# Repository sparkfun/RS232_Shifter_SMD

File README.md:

SparkFun RS232 Shifter SMD
===========================

[*RS232 Shifter SMD(PRT-00449)*](https://www.sparkfun.com/products/449)

This board converts RS232 to TTL and runs from 300 bps to 115200 bps. 
 This will allow a microcontroller to communicate with a computer. 
Shifter SMD is powered from the target application and can run at any voltage! 

Repository Contents
-------------------

* **/Hardware** - All Eagle design files (.brd, .sch)
* **/Production** - Production panel files (.brd)

Documentation
-------------------
* [Serial Communication](https://learn.sparkfun.com/tutorials/serial-communication) - Basic tutorial on serial communication implemented on logic-level (TTL) and RS-232.
* [RS-232 vs. TTL Serial Communication](https://www.sparkfun.com/tutorials/215) - Short explanation about the logic levels and the hardware used to convert signals with the RS232 Shifter. 

Product Versions
----------------
* [PRT-08780](https://www.sparkfun.com/products/8780) - Shifter - no DB9 connector
* [PRT-00449](https://www.sparkfun.com/products/449) - Shifter with DB9 connector populated.

Version History
---------------

* [v1.4](https://github.com/sparkfun/RS232_Shifter_SMD/tree/V_1.4) - GitHub version 1.4. Retired for a more production friendly version.

License Information
-------------------

This product is _**open source**_! 

Please review the LICENSE.md file for license information. 

If you have any questions or concerns on licensing, please contact techsupport@sparkfun.com.

Distributed as-is; no warranty is given.

- Your friends at SparkFun.

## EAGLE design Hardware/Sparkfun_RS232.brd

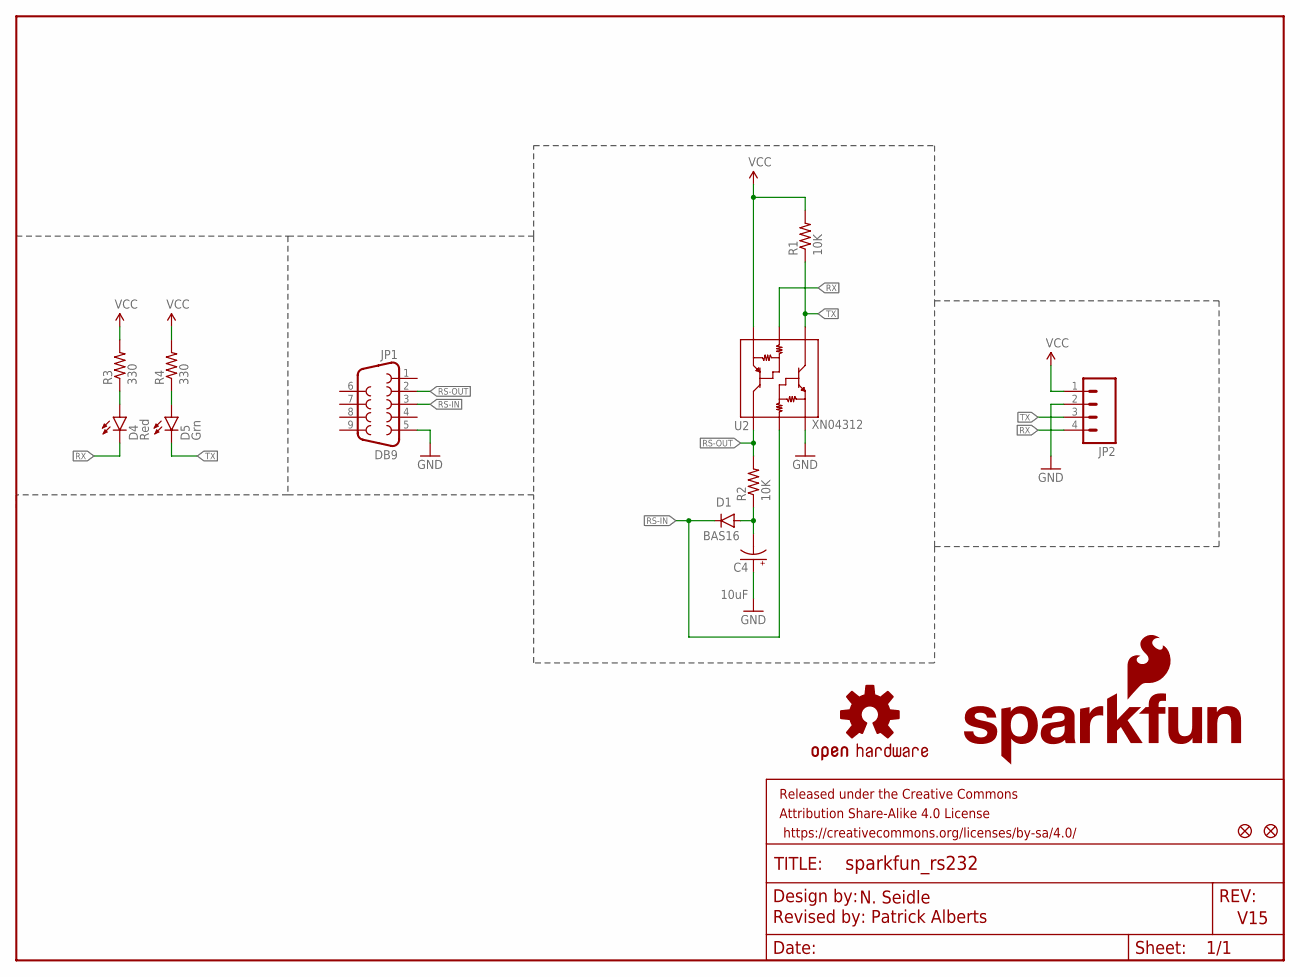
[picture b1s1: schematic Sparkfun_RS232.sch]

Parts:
C4: 10uF; EIA3216
D1: BAS16; SOD-323
D4: Red; LED-1206
D5: Grn; LED-1206
E$1, E$2: FIDUCIAL1X2; FIDUCIAL-1X2
FRAME1: FRAME-LETTER; CREATIVE_COMMONS
JP1: DB9
JP2: M04PTH; 1X04
LOGO1: SFE_LOGO_NAME_FLAME.1_INCH; SFE_LOGO_NAME_FLAME_.1
LOGO2: OSHW-LOGOM; OSHW-LOGO-M
R1, R2: 10K; 0603-RES
R3, R4: 330; 0603-RES
U2: XN04312; SOT23-6

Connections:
GND: C4.A (+), JP1.5, JP2.2, U2.6 (E1)
unnamed: D4.A, R3.1
unnamed: D5.A, R4.1
unnamed: C4.C (-), D1.A, R2.1
RS-IN: D1.C, JP1.3, U2.5 (B1)
RS-OUT: JP1.2, R2.2, U2.4 (C2)
RX: D4.C, JP2.4, U2.2 (B2)
TX: D5.C, JP2.3, R1.1, U2.1 (C1)
VCC: JP2.1, R1.2, R3.2, R4.2, U2.3 (E2)

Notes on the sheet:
V15
Revised by: Patrick Alberts
N. Seidle

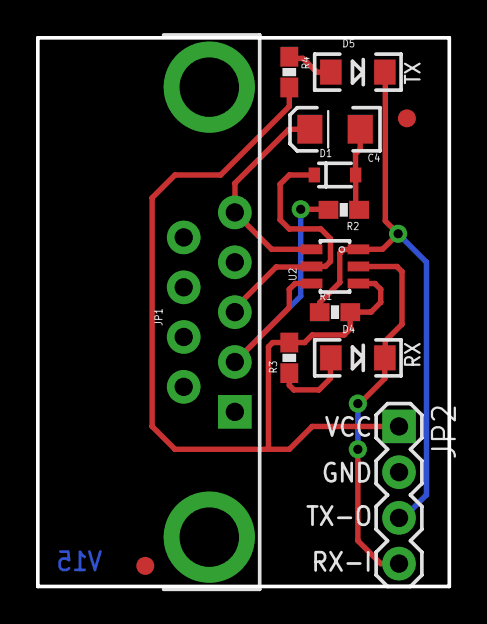
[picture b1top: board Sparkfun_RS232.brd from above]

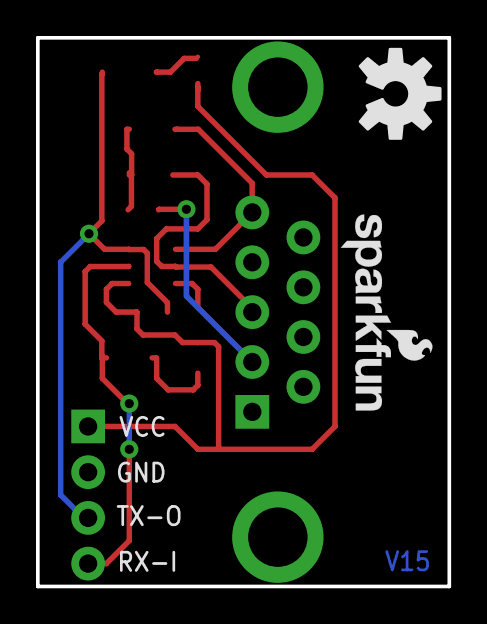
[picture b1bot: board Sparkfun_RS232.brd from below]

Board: 2 copper layers, 22.9 x 30.5 mm, 16 parts (2 on the bottom side), 9 nets.

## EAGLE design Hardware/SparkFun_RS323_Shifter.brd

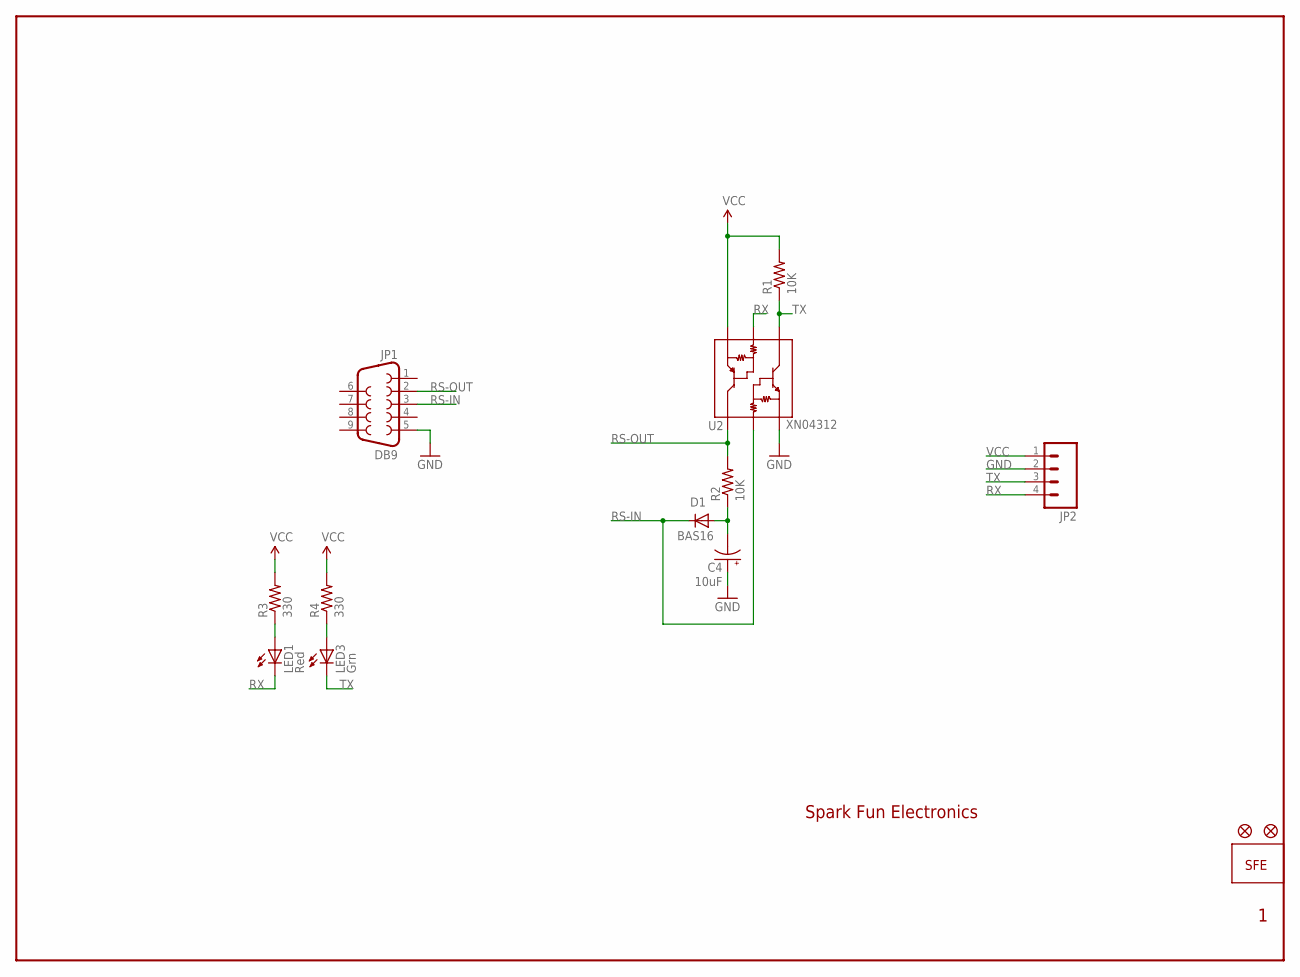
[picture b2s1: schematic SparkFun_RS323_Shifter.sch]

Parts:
C4: 10uF; EIA3216
D1: BAS16; SOD-323
E$1, E$2: FIDUCIAL1X2; FIDUCIAL-1X2
JP1: DB9
JP2: M04PTH; 1X04
LED1: Red; LED-1206
LED3: Grn; LED-1206
R1, R2: 10K; 0603-RES
R3, R4: 330; 0603-RES
U2: XN04312; SOT23-6
U$1: LOGO-SFENEW; SFE-NEW-WEBLOGO

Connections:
GND: C4.A (+), JP1.5, JP2.2, U2.6 (E1)
unnamed: LED1.A, R3.1
unnamed: LED3.A, R4.1
unnamed: C4.C (-), D1.2 (A), R2.1
RS-IN: D1.1 (C), JP1.3, U2.5 (B1)
RS-OUT: JP1.2, R2.2, U2.4 (C2)
RX: JP2.4, LED1.C, U2.2 (B2)
TX: JP2.3, LED3.C, R1.1, U2.1 (C1)
VCC: JP2.1, R1.2, R3.2, R4.2, U2.3 (E2)

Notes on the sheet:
Spark Fun Electronics

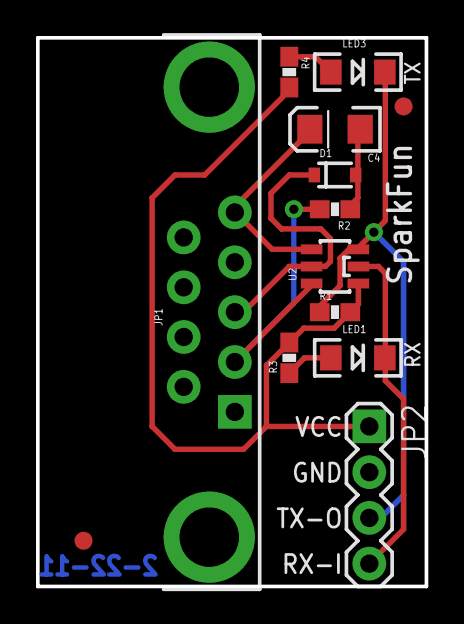
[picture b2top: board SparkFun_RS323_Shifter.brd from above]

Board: 2 copper layers, 21.6 x 30.5 mm, 14 parts (1 on the bottom side), 9 nets.

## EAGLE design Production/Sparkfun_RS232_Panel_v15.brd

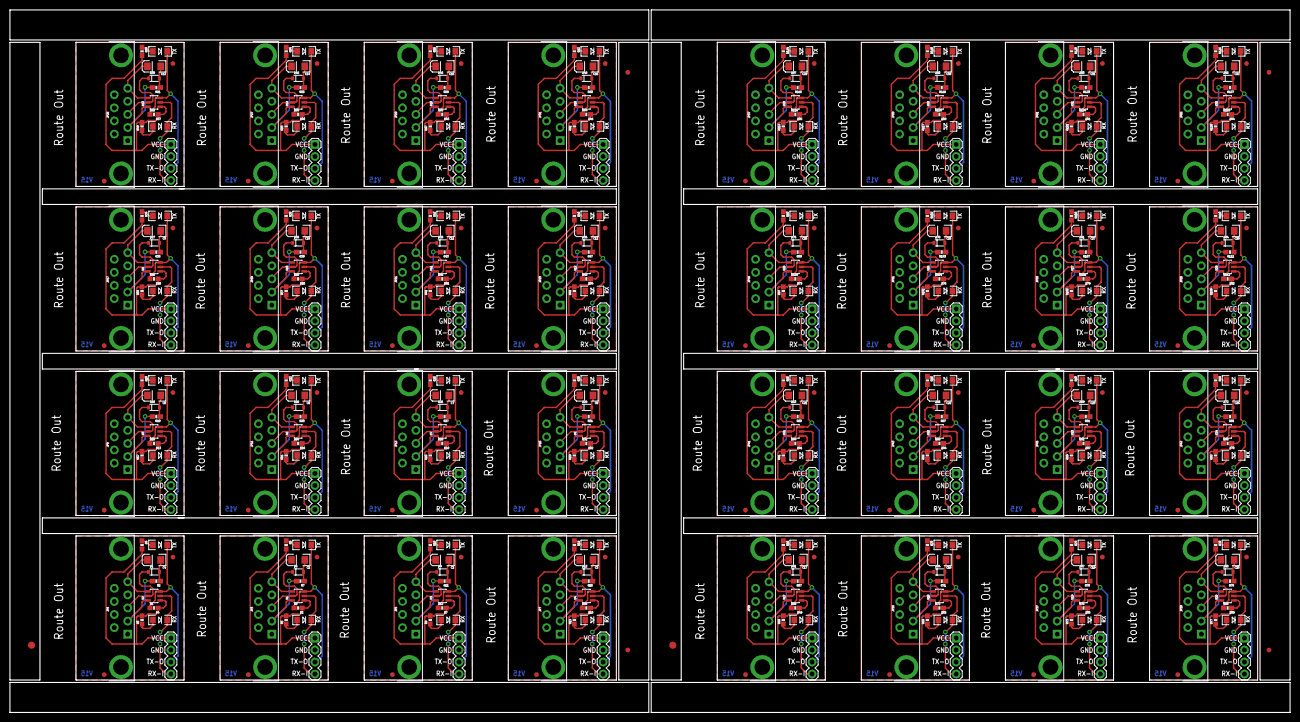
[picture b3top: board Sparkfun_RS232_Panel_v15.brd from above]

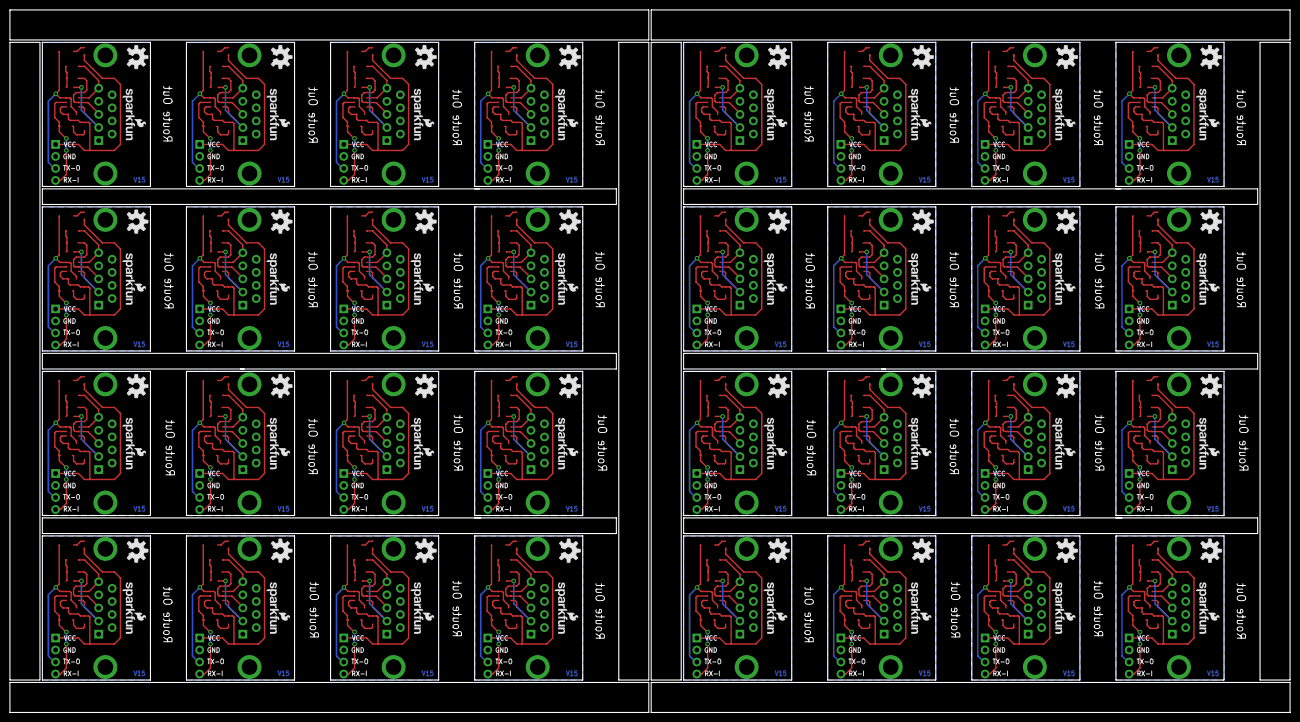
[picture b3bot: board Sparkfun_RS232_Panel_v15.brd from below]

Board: 2 copper layers, 270.8 x 148.6 mm, 486 parts (64 on the bottom side), 288 nets.

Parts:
C1, C2, C3, C4, C5, C6, C7, C8, C9, C10, C11, C12, C13, C14, C15, C16, C17, C18, C19, C20, C21, C22, C23, C24, C25, C26, C27, C28, C29, C30, C31, C32: 10uF; EIA3216
D1, D6, D9, D12, D15, D18, D21, D24, D27, D30, D33, D36, D39, D42, D45, D48, D51, D54, D57, D60, D63, D66, D69, D72, D75, D78, D81, D84, D87, D90, D93, D96: BAS16; SOD-323
D2, D4, D7, D10, D13, D16, D19, D22, D25, D28, D31, D34, D37, D40, D43, D46, D49, D52, D55, D58, D61, D64, D67, D70, D73, D76, D79, D82, D85, D88, D91, D94: Red; LED-1206
D3, D5, D8, D11, D14, D17, D20, D23, D26, D29, D32, D35, D38, D41, D44, D47, D50, D53, D56, D59, D62, D65, D68, D71, D74, D77, D80, D83, D86, D89, D92, D95: Grn; LED-1206
E$1, E$2, E$3, E$4, E$5, E$6, E$7, E$8, E$9, E$10, E$11, E$12, E$13, E$14, E$15, E$16, E$17, E$18, E$19, E$20, E$21, E$22, E$23, E$24, E$25, E$26, E$27, E$28, E$29, E$30, E$31, E$32, E$34, E$35, E$36, E$37, E$38, E$39, E$40, E$41, E$44, E$45, E$46, E$47, E$48, E$49, E$50, E$51, E$52, E$53, E$54, E$55, E$56, E$57, E$58, E$59, E$60, E$61, E$62, E$63, E$64, E$65, E$66, E$67: FIDUCIAL1X2; FIDUCIAL-1X2
E$33, E$70: FIDUCIAL-1.5X3
E$42, E$43, E$68, E$69: FIDUCIAL-1X2
JP1, JP3, JP5, JP7, JP9, JP11, JP13, JP15, JP17, JP19, JP21, JP23, JP25, JP27, JP29, JP31, JP33, JP35, JP37, JP39, JP41, JP43, JP45, JP47, JP49, JP51, JP53, JP55, JP57, JP59, JP61, JP63: DB9
JP2, JP4, JP6, JP8, JP10, JP12, JP14, JP16, JP18, JP20, JP22, JP24, JP26, JP28, JP30, JP32, JP34, JP36, JP38, JP40, JP42, JP44, JP46, JP48, JP50, JP52, JP54, JP56, JP58, JP60, JP62, JP64: 1X04
LOGO1, LOGO4, LOGO6, LOGO8, LOGO10, LOGO12, LOGO14, LOGO16, LOGO18, LOGO20, LOGO22, LOGO24, LOGO26, LOGO28, LOGO30, LOGO32, LOGO34, LOGO36, LOGO38, LOGO40, LOGO42, LOGO44, LOGO46, LOGO48, LOGO50, LOGO52, LOGO54, LOGO56, LOGO58, LOGO60, LOGO62, LOGO64: SFE_LOGO_NAME_FLAME.1_INCH; SFE_LOGO_NAME_FLAME_.1
LOGO2, LOGO3, LOGO5, LOGO7, LOGO9, LOGO11, LOGO13, LOGO15, LOGO17, LOGO19, LOGO21, LOGO23, LOGO25, LOGO27, LOGO29, LOGO31, LOGO33, LOGO35, LOGO37, LOGO39, LOGO41, LOGO43, LOGO45, LOGO47, LOGO49, LOGO51, LOGO53, LOGO55, LOGO57, LOGO59, LOGO61, LOGO63: OSHW-LOGOM; OSHW-LOGO-M
R1, R2, R7, R8, R11, R12, R15, R16, R19, R20, R23, R24, R27, R28, R31, R32, R35, R36, R39, R40, R43, R44, R47, R48, R51, R52, R55, R56, R59, R60, R63, R64, R67, R68, R71, R72, R75, R76, R79, R80, R83, R84, R87, R88, R91, R92, R95, R96, R99, R100, R103, R104, R107, R108, R111, R112, R115, R116, R119, R120, R123, R124, R127, R128: 10K; 0603-RES
R3, R4, R5, R6, R9, R10, R13, R14, R17, R18, R21, R22, R25, R26, R29, R30, R33, R34, R37, R38, R41, R42, R45, R46, R49, R50, R53, R54, R57, R58, R61, R62, R65, R66, R69, R70, R73, R74, R77, R78, R81, R82, R85, R86, R89, R90, R93, R94, R97, R98, R101, R102, R105, R106, R109, R110, R113, R114, R117, R118, R121, R122, R125, R126: 330; 0603-RES
U1, U2, U3, U4, U5, U6, U7, U8, U9, U10, U11, U12, U13, U14, U15, U16, U17, U18, U19, U20, U21, U22, U23, U24, U25, U26, U27, U28, U29, U30, U31, U32: XN04312; SOT23-6

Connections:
GND: C4.A, JP1.5, JP2.2, U2.6
GND1: C1.A, JP3.5, JP4.2, U1.6
GND2: C2.A, JP5.5, JP6.2, U3.6
GND3: C3.A, JP7.5, JP8.2, U4.6
GND4: C5.A, JP9.5, JP10.2, U5.6
GND5: C6.A, JP11.5, JP12.2, U6.6
GND6: C7.A, JP13.5, JP14.2, U7.6
GND7: C8.A, JP15.5, JP16.2, U8.6
GND8: C9.A, JP17.5, JP18.2, U9.6
GND9: C10.A, JP19.5, JP20.2, U10.6
GND10: C11.A, JP21.5, JP22.2, U11.6
GND11: C12.A, JP23.5, JP24.2, U12.6
GND12: C13.A, JP25.5, JP26.2, U13.6
GND13: C14.A, JP27.5, JP28.2, U14.6
GND14: C15.A, JP29.5, JP30.2, U15.6
GND15: C16.A, JP31.5, JP32.2, U16.6
GND16: C17.A, JP33.5, JP34.2, U17.6
GND17: C18.A, JP35.5, JP36.2, U18.6
GND18: C19.A, JP37.5, JP38.2, U19.6
GND19: C20.A, JP39.5, JP40.2, U20.6
GND20: C21.A, JP41.5, JP42.2, U21.6
GND21: C22.A, JP43.5, JP44.2, U22.6
GND22: C23.A, JP45.5, JP46.2, U23.6
GND23: C24.A, JP47.5, JP48.2, U24.6
GND24: C25.A, JP49.5, JP50.2, U25.6
GND25: C26.A, JP51.5, JP52.2, U26.6
GND26: C27.A, JP53.5, JP54.2, U27.6
GND27: C28.A, JP55.5, JP56.2, U28.6
GND28: C29.A, JP57.5, JP58.2, U29.6
GND29: C30.A, JP59.5, JP60.2, U30.6
GND30: C31.A, JP61.5, JP62.2, U31.6
GND31: C32.A, JP63.5, JP64.2, U32.6
unnamed: D4.A, R3.1
unnamed: D5.A, R4.1
unnamed: D2.A, R5.1
unnamed: C4.C, D1.A, R2.1
unnamed: D3.A, R6.1
unnamed: C1.C, D6.A, R7.1
unnamed: D7.A, R9.1
unnamed: D8.A, R10.1
unnamed: C2.C, D9.A, R11.1
unnamed: D10.A, R13.1
unnamed: D11.A, R14.1
unnamed: C3.C, D12.A, R15.1
unnamed: D13.A, R17.1
unnamed: D14.A, R18.1
unnamed: C5.C, D15.A, R19.1
unnamed: D16.A, R21.1
unnamed: D17.A, R22.1
unnamed: C6.C, D18.A, R23.1
unnamed: D19.A, R25.1
unnamed: D20.A, R26.1
unnamed: C7.C, D21.A, R27.1
unnamed: D22.A, R29.1
unnamed: D23.A, R30.1
unnamed: C8.C, D24.A, R31.1
unnamed: D25.A, R33.1
unnamed: D26.A, R34.1
unnamed: C9.C, D27.A, R35.1
unnamed: D28.A, R37.1
unnamed: D29.A, R38.1
unnamed: C10.C, D30.A, R39.1
unnamed: D31.A, R41.1
unnamed: D32.A, R42.1
unnamed: C11.C, D33.A, R43.1
unnamed: D34.A, R45.1
unnamed: D35.A, R46.1
unnamed: C12.C, D36.A, R47.1
unnamed: D37.A, R49.1
unnamed: D38.A, R50.1
unnamed: C13.C, D39.A, R51.1
unnamed: D40.A, R53.1
unnamed: D41.A, R54.1
unnamed: C14.C, D42.A, R55.1
unnamed: D43.A, R57.1
unnamed: D44.A, R58.1
unnamed: C15.C, D45.A, R59.1
unnamed: D46.A, R61.1
unnamed: D47.A, R62.1
unnamed: C16.C, D48.A, R63.1
unnamed: D49.A, R65.1
unnamed: D50.A, R66.1
unnamed: C17.C, D51.A, R67.1
unnamed: D52.A, R69.1
unnamed: D53.A, R70.1
unnamed: C18.C, D54.A, R71.1
unnamed: D55.A, R73.1
unnamed: D56.A, R74.1
unnamed: C19.C, D57.A, R75.1
unnamed: D58.A, R77.1
unnamed: D59.A, R78.1
unnamed: C20.C, D60.A, R79.1
unnamed: D61.A, R81.1
unnamed: D62.A, R82.1
unnamed: C21.C, D63.A, R83.1
unnamed: D64.A, R85.1
unnamed: D65.A, R86.1
unnamed: C22.C, D66.A, R87.1
unnamed: D67.A, R89.1
unnamed: D68.A, R90.1
unnamed: C23.C, D69.A, R91.1
unnamed: D70.A, R93.1
unnamed: D71.A, R94.1
unnamed: C24.C, D72.A, R95.1
unnamed: D73.A, R97.1
unnamed: D74.A, R98.1
unnamed: C25.C, D75.A, R99.1
unnamed: D76.A, R101.1
unnamed: D77.A, R102.1
unnamed: C26.C, D78.A, R103.1
unnamed: D79.A, R105.1
unnamed: D80.A, R106.1
unnamed: C27.C, D81.A, R107.1
unnamed: D82.A, R109.1
unnamed: D83.A, R110.1
unnamed: C28.C, D84.A, R111.1
unnamed: D85.A, R113.1
unnamed: D86.A, R114.1
unnamed: C29.C, D87.A, R115.1
unnamed: D88.A, R117.1
unnamed: D89.A, R118.1
unnamed: C30.C, D90.A, R119.1
unnamed: D91.A, R121.1
unnamed: D92.A, R122.1
unnamed: C31.C, D93.A, R123.1
unnamed: D94.A, R125.1
unnamed: D95.A, R126.1
unnamed: C32.C, D96.A, R127.1
RS-IN: D1.C, JP1.3, U2.5
RS-IN1: D6.C, JP3.3, U1.5
RS-IN2: D9.C, JP5.3, U3.5
RS-IN3: D12.C, JP7.3, U4.5
RS-IN4: D15.C, JP9.3, U5.5
RS-IN5: D18.C, JP11.3, U6.5
RS-IN6: D21.C, JP13.3, U7.5
RS-IN7: D24.C, JP15.3, U8.5
RS-IN8: D27.C, JP17.3, U9.5
RS-IN9: D30.C, JP19.3, U10.5
RS-IN10: D33.C, JP21.3, U11.5
RS-IN11: D36.C, JP23.3, U12.5
RS-IN12: D39.C, JP25.3, U13.5
RS-IN13: D42.C, JP27.3, U14.5
RS-IN14: D45.C, JP29.3, U15.5
RS-IN15: D48.C, JP31.3, U16.5
RS-IN16: D51.C, JP33.3, U17.5
RS-IN17: D54.C, JP35.3, U18.5
RS-IN18: D57.C, JP37.3, U19.5
RS-IN19: D60.C, JP39.3, U20.5
RS-IN20: D63.C, JP41.3, U21.5
RS-IN21: D66.C, JP43.3, U22.5
RS-IN22: D69.C, JP45.3, U23.5
RS-IN23: D72.C, JP47.3, U24.5
RS-IN24: D75.C, JP49.3, U25.5
RS-IN25: D78.C, JP51.3, U26.5
RS-IN26: D81.C, JP53.3, U27.5
RS-IN27: D84.C, JP55.3, U28.5
RS-IN28: D87.C, JP57.3, U29.5
RS-IN29: D90.C, JP59.3, U30.5
RS-IN30: D93.C, JP61.3, U31.5
RS-IN31: D96.C, JP63.3, U32.5
RS-OUT: JP1.2, R2.2, U2.4
RS-OUT1: JP3.2, R7.2, U1.4
RS-OUT2: JP5.2, R11.2, U3.4
RS-OUT3: JP7.2, R15.2, U4.4
RS-OUT4: JP9.2, R19.2, U5.4
RS-OUT5: JP11.2, R23.2, U6.4
RS-OUT6: JP13.2, R27.2, U7.4
RS-OUT7: JP15.2, R31.2, U8.4
RS-OUT8: JP17.2, R35.2, U9.4
RS-OUT9: JP19.2, R39.2, U10.4
RS-OUT10: JP21.2, R43.2, U11.4
RS-OUT11: JP23.2, R47.2, U12.4
RS-OUT12: JP25.2, R51.2, U13.4
RS-OUT13: JP27.2, R55.2, U14.4
RS-OUT14: JP29.2, R59.2, U15.4
RS-OUT15: JP31.2, R63.2, U16.4
RS-OUT16: JP33.2, R67.2, U17.4
RS-OUT17: JP35.2, R71.2, U18.4
RS-OUT18: JP37.2, R75.2, U19.4
RS-OUT19: JP39.2, R79.2, U20.4
RS-OUT20: JP41.2, R83.2, U21.4
RS-OUT21: JP43.2, R87.2, U22.4
RS-OUT22: JP45.2, R91.2, U23.4
RS-OUT23: JP47.2, R95.2, U24.4
RS-OUT24: JP49.2, R99.2, U25.4
RS-OUT25: JP51.2, R103.2, U26.4
RS-OUT26: JP53.2, R107.2, U27.4
RS-OUT27: JP55.2, R111.2, U28.4
RS-OUT28: JP57.2, R115.2, U29.4
RS-OUT29: JP59.2, R119.2, U30.4
RS-OUT30: JP61.2, R123.2, U31.4
RS-OUT31: JP63.2, R127.2, U32.4
RX: D4.C, JP2.4, U2.2
RX1: D2.C, JP4.4, U1.2
RX2: D7.C, JP6.4, U3.2
RX3: D10.C, JP8.4, U4.2
RX4: D13.C, JP10.4, U5.2
RX5: D16.C, JP12.4, U6.2
RX6: D19.C, JP14.4, U7.2
RX7: D22.C, JP16.4, U8.2
RX8: D25.C, JP18.4, U9.2
RX9: D28.C, JP20.4, U10.2
RX10: D31.C, JP22.4, U11.2
RX11: D34.C, JP24.4, U12.2
RX12: D37.C, JP26.4, U13.2
RX13: D40.C, JP28.4, U14.2
RX14: D43.C, JP30.4, U15.2
RX15: D46.C, JP32.4, U16.2
RX16: D49.C, JP34.4, U17.2
RX17: D52.C, JP36.4, U18.2
RX18: D55.C, JP38.4, U19.2
RX19: D58.C, JP40.4, U20.2
RX20: D61.C, JP42.4, U21.2
RX21: D64.C, JP44.4, U22.2
RX22: D67.C, JP46.4, U23.2
RX23: D70.C, JP48.4, U24.2
RX24: D73.C, JP50.4, U25.2
RX25: D76.C, JP52.4, U26.2
RX26: D79.C, JP54.4, U27.2
RX27: D82.C, JP56.4, U28.2
RX28: D85.C, JP58.4, U29.2
RX29: D88.C, JP60.4, U30.2
RX30: D91.C, JP62.4, U31.2
RX31: D94.C, JP64.4, U32.2
TX: D5.C, JP2.3, R1.1, U2.1
TX1: D3.C, JP4.3, R8.1, U1.1
TX2: D8.C, JP6.3, R12.1, U3.1
TX3: D11.C, JP8.3, R16.1, U4.1
TX4: D14.C, JP10.3, R20.1, U5.1
TX5: D17.C, JP12.3, R24.1, U6.1
TX6: D20.C, JP14.3, R28.1, U7.1
TX7: D23.C, JP16.3, R32.1, U8.1
TX8: D26.C, JP18.3, R36.1, U9.1
TX9: D29.C, JP20.3, R40.1, U10.1
TX10: D32.C, JP22.3, R44.1, U11.1
TX11: D35.C, JP24.3, R48.1, U12.1
TX12: D38.C, JP26.3, R52.1, U13.1
TX13: D41.C, JP28.3, R56.1, U14.1
TX14: D44.C, JP30.3, R60.1, U15.1
TX15: D47.C, JP32.3, R64.1, U16.1
TX16: D50.C, JP34.3, R68.1, U17.1
TX17: D53.C, JP36.3, R72.1, U18.1
TX18: D56.C, JP38.3, R76.1, U19.1
TX19: D59.C, JP40.3, R80.1, U20.1
TX20: D62.C, JP42.3, R84.1, U21.1
TX21: D65.C, JP44.3, R88.1, U22.1
TX22: D68.C, JP46.3, R92.1, U23.1
TX23: D71.C, JP48.3, R96.1, U24.1
TX24: D74.C, JP50.3, R100.1, U25.1
TX25: D77.C, JP52.3, R104.1, U26.1
TX26: D80.C, JP54.3, R108.1, U27.1
TX27: D83.C, JP56.3, R112.1, U28.1
TX28: D86.C, JP58.3, R116.1, U29.1
TX29: D89.C, JP60.3, R120.1, U30.1
TX30: D92.C, JP62.3, R124.1, U31.1
TX31: D95.C, JP64.3, R128.1, U32.1
VCC: JP2.1, R1.2, R3.2, R4.2, U2.3
VCC1: JP4.1, R5.2, R6.2, R8.2, U1.3
VCC2: JP6.1, R9.2, R10.2, R12.2, U3.3
VCC3: JP8.1, R13.2, R14.2, R16.2, U4.3
VCC4: JP10.1, R17.2, R18.2, R20.2, U5.3
VCC5: JP12.1, R21.2, R22.2, R24.2, U6.3
VCC6: JP14.1, R25.2, R26.2, R28.2, U7.3
VCC7: JP16.1, R29.2, R30.2, R32.2, U8.3
VCC8: JP18.1, R33.2, R34.2, R36.2, U9.3
VCC9: JP20.1, R37.2, R38.2, R40.2, U10.3
VCC10: JP22.1, R41.2, R42.2, R44.2, U11.3
VCC11: JP24.1, R45.2, R46.2, R48.2, U12.3
VCC12: JP26.1, R49.2, R50.2, R52.2, U13.3
VCC13: JP28.1, R53.2, R54.2, R56.2, U14.3
VCC14: JP30.1, R57.2, R58.2, R60.2, U15.3
VCC15: JP32.1, R61.2, R62.2, R64.2, U16.3
VCC16: JP34.1, R65.2, R66.2, R68.2, U17.3
VCC17: JP36.1, R69.2, R70.2, R72.2, U18.3
VCC18: JP38.1, R73.2, R74.2, R76.2, U19.3
VCC19: JP40.1, R77.2, R78.2, R80.2, U20.3
VCC20: JP42.1, R81.2, R82.2, R84.2, U21.3
VCC21: JP44.1, R85.2, R86.2, R88.2, U22.3
VCC22: JP46.1, R89.2, R90.2, R92.2, U23.3
VCC23: JP48.1, R93.2, R94.2, R96.2, U24.3
VCC24: JP50.1, R97.2, R98.2, R100.2, U25.3
VCC25: JP52.1, R101.2, R102.2, R104.2, U26.3
VCC26: JP54.1, R105.2, R106.2, R108.2, U27.3
VCC27: JP56.1, R109.2, R110.2, R112.2, U28.3
VCC28: JP58.1, R113.2, R114.2, R116.2, U29.3
VCC29: JP60.1, R117.2, R118.2, R120.2, U30.3
VCC30: JP62.1, R121.2, R122.2, R124.2, U31.3
VCC31: JP64.1, R125.2, R126.2, R128.2, U32.3

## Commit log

2014-01-09 Initial commit of board files and README
2014-11-05 Initial Commit with BRD/SCH with additional changes
    Added version number, removed old sparkfun logo, updated SF logo on the
    back as well as added oshw logo. Sch cleanup as well.
2014-11-05 Initial Commit with BRD/SCH
2014-11-06 New brd/sch commit
2014-11-06 0603/SCH update, Trace redo
2014-11-06 New files
2014-11-11 Fixed headers, trace re route
2015-01-20 Fixed bad trace.
2015-01-21 fixed bad trace, added top ground plane.
2015-03-05 qc CL items fixed.
2015-03-11 Adding current board files, updating README
2015-03-25 fixed trace width.
2015-03-25 fixed trace width
2015-03-26 updated logo
2015-03-26 created panel v15
2015-09-01 Fixing product link in README
2015-09-01 Fixing layout in README
2025-06-27 Update README.md
    Updating link

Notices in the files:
parts and their libraries:
SparkFun-Resistors: Licensing: Creative Commons ShareAlike 4.0 International - https://creativecommons.org/licenses/by-sa/4.0
SparkFun-Aesthetics: Released under the Creative Commons Attribution Share-Alike 4.0 License
SparkFun-Aesthetics: https://creativecommons.org/licenses/by-sa/4.0
